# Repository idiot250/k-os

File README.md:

# k-OS

k-OS is a standalone digital sound instrument. the primary sound qualities i was looking for were experimental, a bit aggressive style edm, taking inspiration from tracks like luvcore dlux by MIDNIGHT CLUB. its intended sound palette combines distorted bass, harsh/resonant leads, noisy textures, and evolving rhythms. 

i built this because i wanted to find edm i liked for a long time, but while many were inspirational, i didn't find many that fit my very specific criteria. 

k-OS is designed around two operating modes, play and generate. play directly triggers notes and manipulates sound using physical controls, whilst generative produces rhythms with controls for changing params (tempo, sound energy, scales, effects, glitch etc).

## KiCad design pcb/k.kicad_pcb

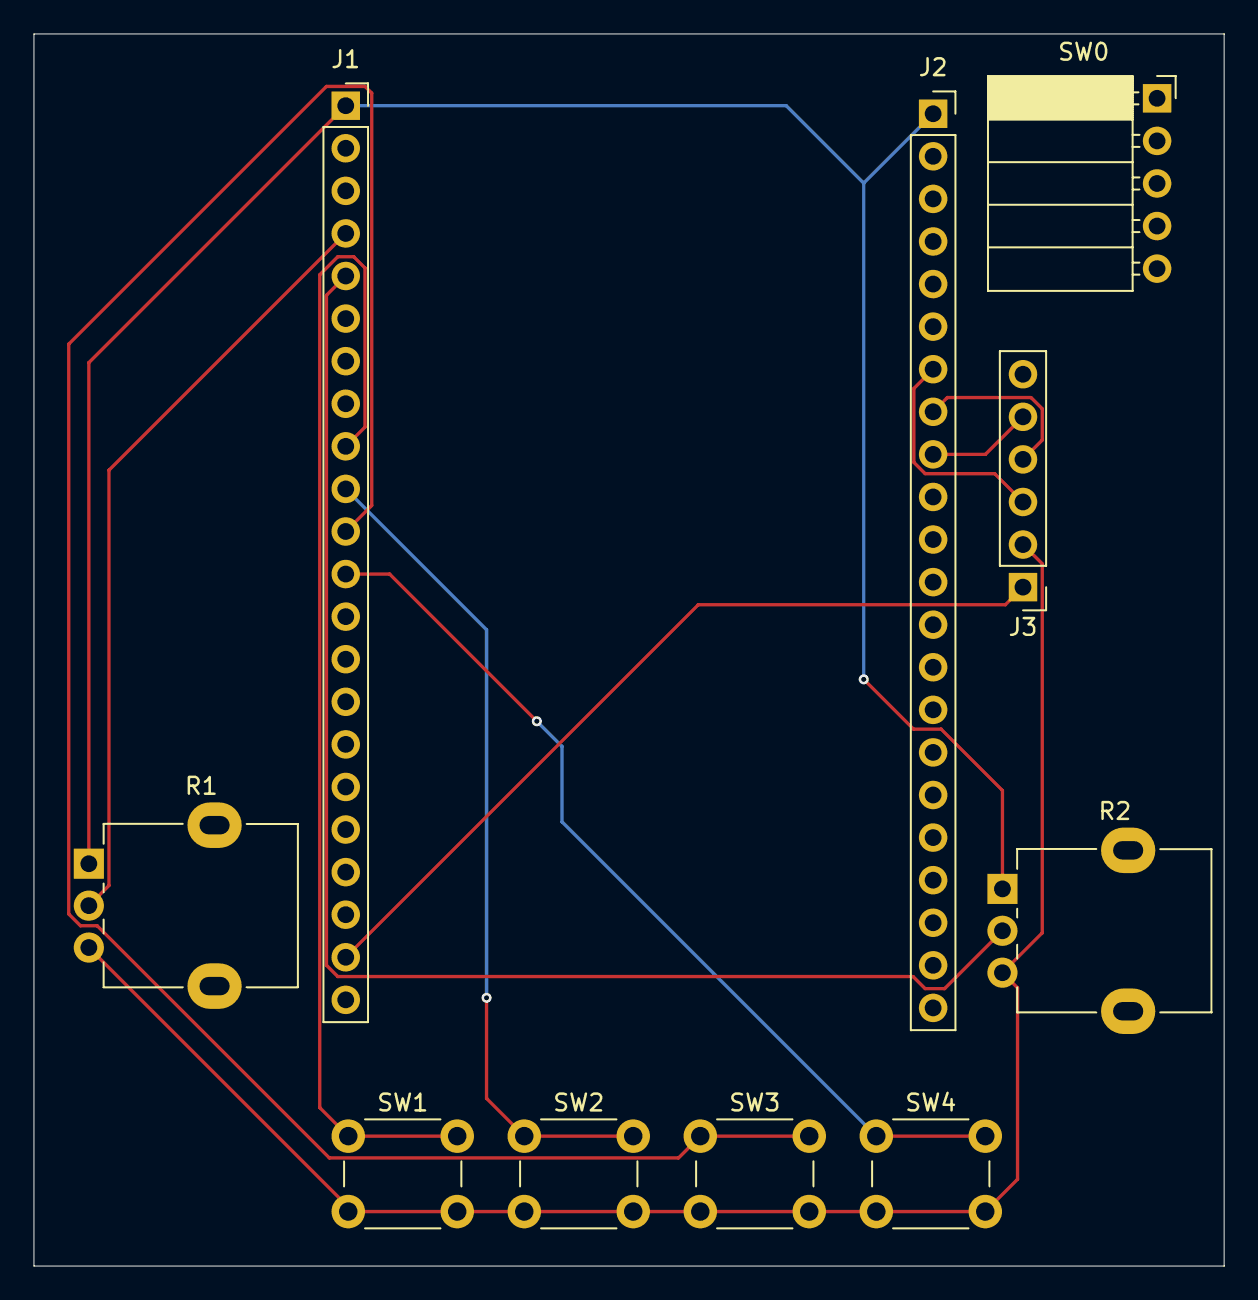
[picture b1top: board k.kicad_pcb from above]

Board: 2 copper layers, 71.0 x 73.5 mm, 10 parts (0 on the bottom side), 12 nets.

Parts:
J1: ESP32-S3 RIGHT; PinSocket_1x22_P2.54mm_Vertical
J2: ESP32-S3 LEFT; PinSocket_1x22_P2.54mm_Vertical
J3: PCM5102A DAC MODULE; PinHeader_1x06_P2.54mm_Vertical
R1, R2: 10k; Potentiometer_Alpha_RD901F-40-00D_Single_Vertical
SW0: RotaryEncoder_Switch; PinSocket_1x05_P2.54mm_Horizontal
SW1: PLAY; SW_PUSH_6mm_H5mm
SW2: TRACK; SW_PUSH_6mm_H5mm
SW3: MODE; SW_PUSH_6mm_H5mm
SW4: STEP; SW_PUSH_6mm_H5mm

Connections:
+3.3V: J1.1, J2.1, R1.1, R2.1
/BTN_MODE: J1.11, SW3.1
/BTN_PLAY: J1.9, SW1.1
/BTN_STEP: J1.12, SW4.1
/BTN_TRACK: J1.10, SW2.1
/DAC_VIN: J1.21, J3.1
/I2S_BCLK: J2.7, J3.3
/I2S_DOUT: J2.9, J3.5
/I2S_LRCK: J2.8, J3.4
/POT_DIST: J1.5, R2.2
/POT_TEMPO: J1.4, R1.2
GND: J3.2, R1.3, R2.3, SW1.2, SW2.2, SW3.2, SW4.2
